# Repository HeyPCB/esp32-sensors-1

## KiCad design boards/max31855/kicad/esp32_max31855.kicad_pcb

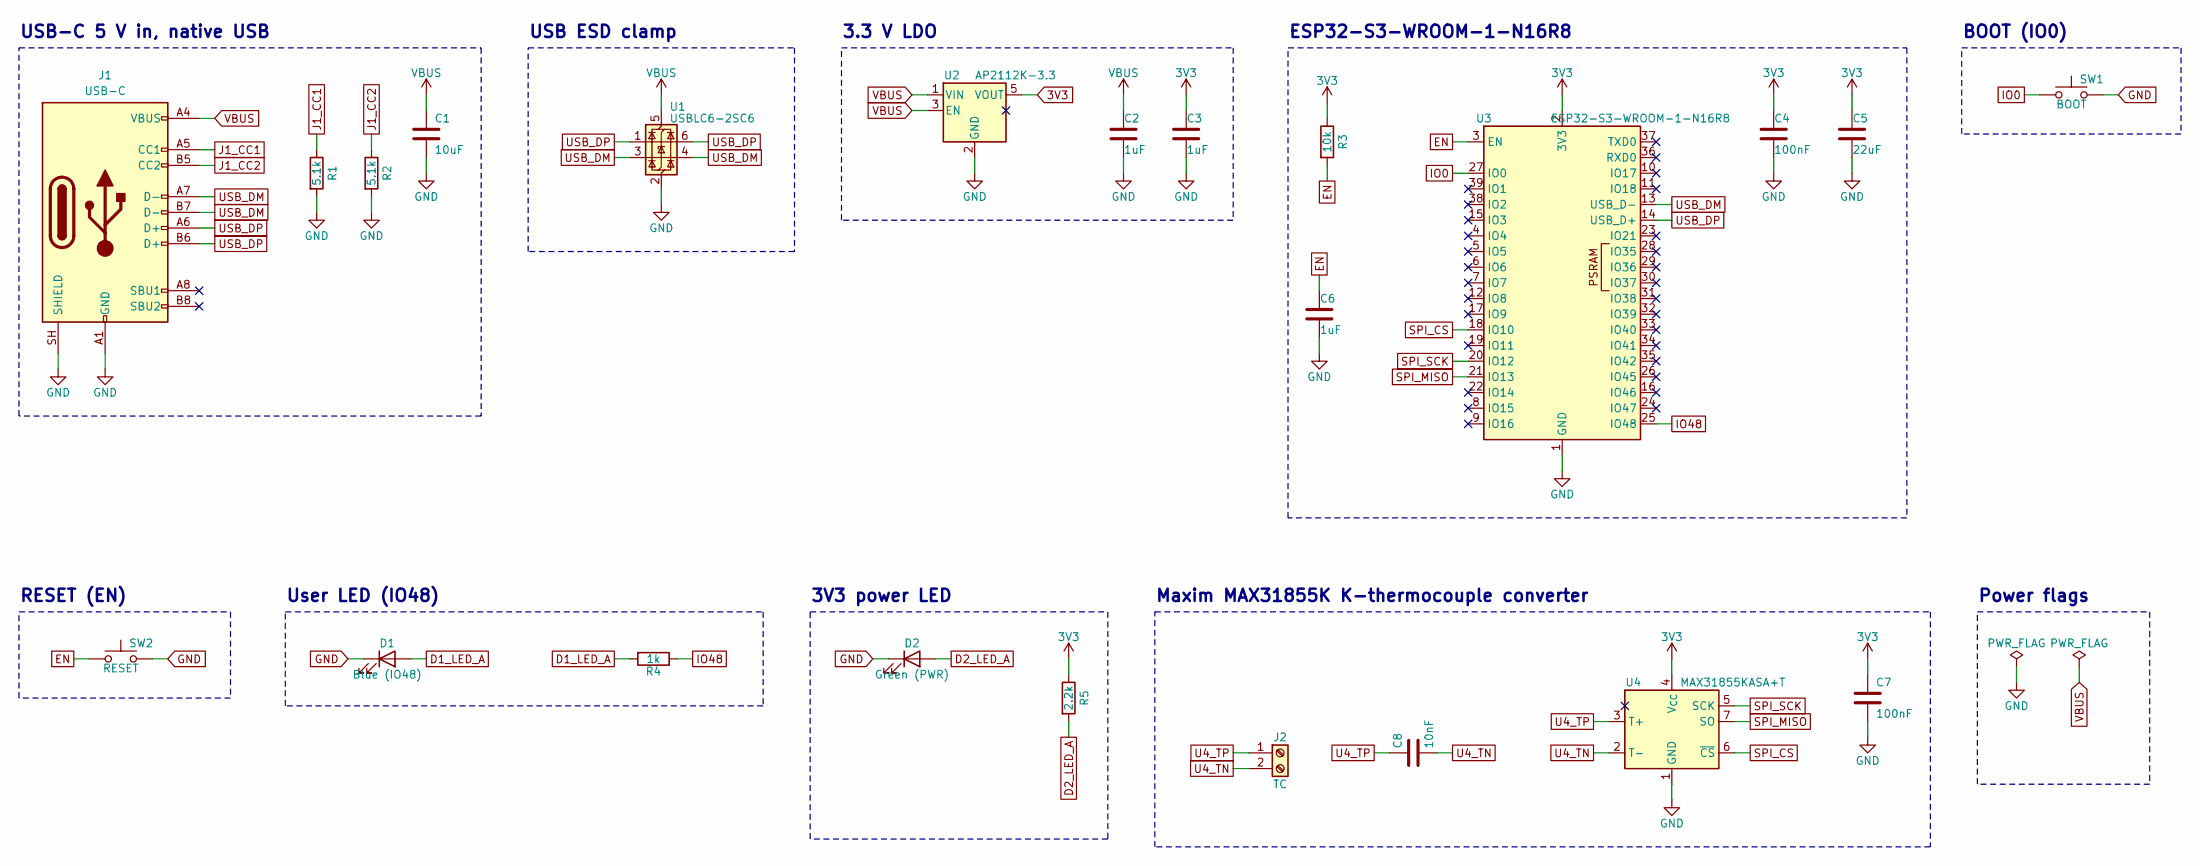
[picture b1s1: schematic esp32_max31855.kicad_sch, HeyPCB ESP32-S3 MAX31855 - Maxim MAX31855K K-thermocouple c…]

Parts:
C1: 10uF; C_0805_2012Metric; MPN CL21A106KAYNNNE; LCSC C15850
C2, C3, C6: 1uF; C_0603_1608Metric; MPN CL10A105KB8NNNC; LCSC C15849
C4: 100nF; C_0603_1608Metric; MPN CC0603KRX7R9BB104; LCSC C14663
C5: 22uF; C_0805_2012Metric; MPN CL21A226MAQNNNE; LCSC C45783
C7: 100nF; C_0402_1005Metric; MPN CL05B104KO5NNNC; LCSC C1525
C8: 10nF; C_0402_1005Metric; MPN CL05B103KB5NNNC; LCSC C15195
D1: Blue (IO48); LED_0603_1608Metric; MPN NCD0603B1; LCSC C84266
D2: Green (PWR); LED_0603_1608Metric; MPN KT-0603G; LCSC C12624
J1: USB-C; USB_C_Receptacle_HRO_TYPE-C-31-M-12; MPN TYPE-C-31-M-12; LCSC C165948
J2: TC; TerminalBlock_MaiXu_MX126-5.0-02P_1x02_P5.00mm; MPN MX126-5.0-02P-GN01-Cu-S-A; LCSC C5188434
R1, R2: 5.1k; R_0402_1005Metric; MPN 0402WGF5101TCE; LCSC C25905
R3: 10k; R_0603_1608Metric; MPN 0603WAF1002T5E; LCSC C25804
R4: 1k; R_0603_1608Metric; MPN 0603WAF1001T5E; LCSC C21190
R5: 2.2k; R_0603_1608Metric; MPN 0603WAF2201T5E; LCSC C4190
SW1: BOOT; SW_Push_1P1T_XKB_TS-1187A; MPN TS-1187A-B-A-B; LCSC C318884
SW2: RESET; SW_Push_1P1T_XKB_TS-1187A; MPN TS-1187A-B-A-B; LCSC C318884
U1: USBLC6-2SC6; SOT-23-6; MPN USBLC6-2SC6; LCSC C7519
U2: AP2112K-3.3; SOT-23-5; MPN AP2112K-3.3TRG1; LCSC C51118
U3: ESP32-S3-WROOM-1-N16R8; ESP32-S3-WROOM-1; MPN ESP32-S3-WROOM-1-N16R8; LCSC C2913202
U4: MAX31855KASA+T; SOIC-8_3.9x4.9mm_P1.27mm; MPN MAX31855KASA+T; LCSC C52028

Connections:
3V3: C3.1, C4.1, C5.1, C7.1, R3.1, R5.1, U2.5 (VOUT), U3.2 (3V3), U4.4 (V_{CC})
D1_LED_A: D1.2 (A), R4.2
D2_LED_A: D2.2 (A), R5.2
EN: C6.1, R3.2, SW2.1, U3.3 (EN)
GND: C1.2, C2.2, C3.2, C4.2, C5.2, C6.2, C7.2, D1.1 (K), D2.1 (K), J1.A1 (GND), J1.A12 (GND), J1.B1 (GND), J1.B12 (GND), J1.SH (SHIELD), R1.2, R2.2, SW1.2, SW2.2, U1.2 (GND), U2.2 (GND), U3.1 (GND), U3.40 (GND), U3.41 (GND), U4.1 (GND)
IO0: SW1.1, U3.27 (IO0)
IO48: R4.1, U3.25 (IO48)
J1_CC1: J1.A5 (CC1), R1.1
J1_CC2: J1.B5 (CC2), R2.1
SPI_CS: U3.18 (IO10), U4.6 (~CS)
SPI_MISO: U3.21 (IO13), U4.7 (SO)
SPI_SCK: U3.20 (IO12), U4.5 (SCK)
U4_TN: C8.2, J2.2, U4.2 (T-)
U4_TP: C8.1, J2.1, U4.3 (T+)
USB_DM: J1.A7 (D-), J1.B7 (D-), U1.3 (I/O2), U1.4 (I/O2), U3.13 (USB_D-)
USB_DP: J1.A6 (D+), J1.B6 (D+), U1.1 (I/O1), U1.6 (I/O1), U3.14 (USB_D+)
VBUS: C1.1, C2.1, J1.A4 (VBUS), J1.A9 (VBUS), J1.B4 (VBUS), J1.B9 (VBUS), U1.5 (VBUS), U2.1 (VIN), U2.3 (EN)

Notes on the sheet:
USB-C 5 V in, native USB
USB ESD clamp
3.3 V LDO
ESP32-S3-WROOM-1-N16R8
BOOT (IO0)
RESET (EN)
User LED (IO48)
3V3 power LED
Maxim MAX31855K K-thermocouple converter
Power flags

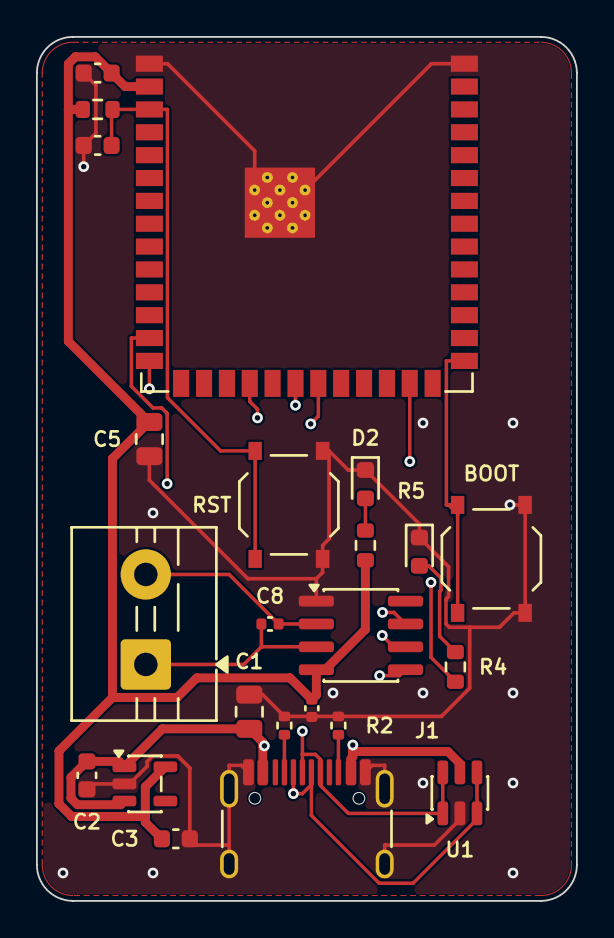
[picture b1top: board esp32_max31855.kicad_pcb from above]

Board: 4 copper layers, 30.0 x 48.0 mm, 23 parts (0 on the bottom side), 17 nets.

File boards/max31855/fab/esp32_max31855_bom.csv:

"Reference","Value","Footprint","MPN","LCSC","Qty"
"C1","10uF","Capacitor_SMD:C_0805_2012Metric","CL21A106KAYNNNE","C15850","1"
"C2,C3,C6","1uF","Capacitor_SMD:C_0603_1608Metric","CL10A105KB8NNNC","C15849","3"
"C4","100nF","Capacitor_SMD:C_0603_1608Metric","CC0603KRX7R9BB104","C14663","1"
"C5","22uF","Capacitor_SMD:C_0805_2012Metric","CL21A226MAQNNNE","C45783","1"
"C7","100nF","Capacitor_SMD:C_0402_1005Metric","CL05B104KO5NNNC","C1525","1"
"C8","10nF","Capacitor_SMD:C_0402_1005Metric","CL05B103KB5NNNC","C15195","1"
"D1","Blue (IO48)","LED_SMD:LED_0603_1608Metric","NCD0603B1","C84266","1"
"D2","Green (PWR)","LED_SMD:LED_0603_1608Metric","KT-0603G","C12624","1"
"J1","USB-C","Connector_USB:USB_C_Receptacle_HRO_TYPE-C-31-M-12","TYPE-C-31-M-12","C165948","1"
"J2","TC","TerminalBlock:TerminalBlock_MaiXu_MX126-5.0-02P_1x02_P5.00mm","MX126-5.0-02P-GN01-Cu-S-A","C5188434","1"
"R1,R2","5.1k","Resistor_SMD:R_0402_1005Metric","0402WGF5101TCE","C25905","2"
"R3","10k","Resistor_SMD:R_0603_1608Metric","0603WAF1002T5E","C25804","1"
"R4","1k","Resistor_SMD:R_0603_1608Metric","0603WAF1001T5E","C21190","1"
"R5","2.2k","Resistor_SMD:R_0603_1608Metric","0603WAF2201T5E","C4190","1"
"SW1","BOOT","Button_Switch_SMD:SW_Push_1P1T_XKB_TS-1187A","TS-1187A-B-A-B","C318884","1"
"SW2","RESET","Button_Switch_SMD:SW_Push_1P1T_XKB_TS-1187A","TS-1187A-B-A-B","C318884","1"
"U1","USBLC6-2SC6","Package_TO_SOT_SMD:SOT-23-6","USBLC6-2SC6","C7519","1"
"U2","AP2112K-3.3","Package_TO_SOT_SMD:SOT-23-5","AP2112K-3.3TRG1","C51118","1"
"U3","ESP32-S3-WROOM-1-N16R8","RF_Module:ESP32-S3-WROOM-1","ESP32-S3-WROOM-1-N16R8","C2913202","1"
"U4","MAX31855KASA+T","Package_SO:SOIC-8_3.9x4.9mm_P1.27mm","MAX31855KASA+T","C52028","1"
